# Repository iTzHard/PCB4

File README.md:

# PCB4

Minimalist 38 key keyboard designed for BVC2013, the layout is derived from The Card by Ben Vallack.

I don't plan to order this design, feel free to bug me on Discord or Twitter if you find any problems or need any help.

[Absolem Club](https://discord.gg/JM7XwHd746)

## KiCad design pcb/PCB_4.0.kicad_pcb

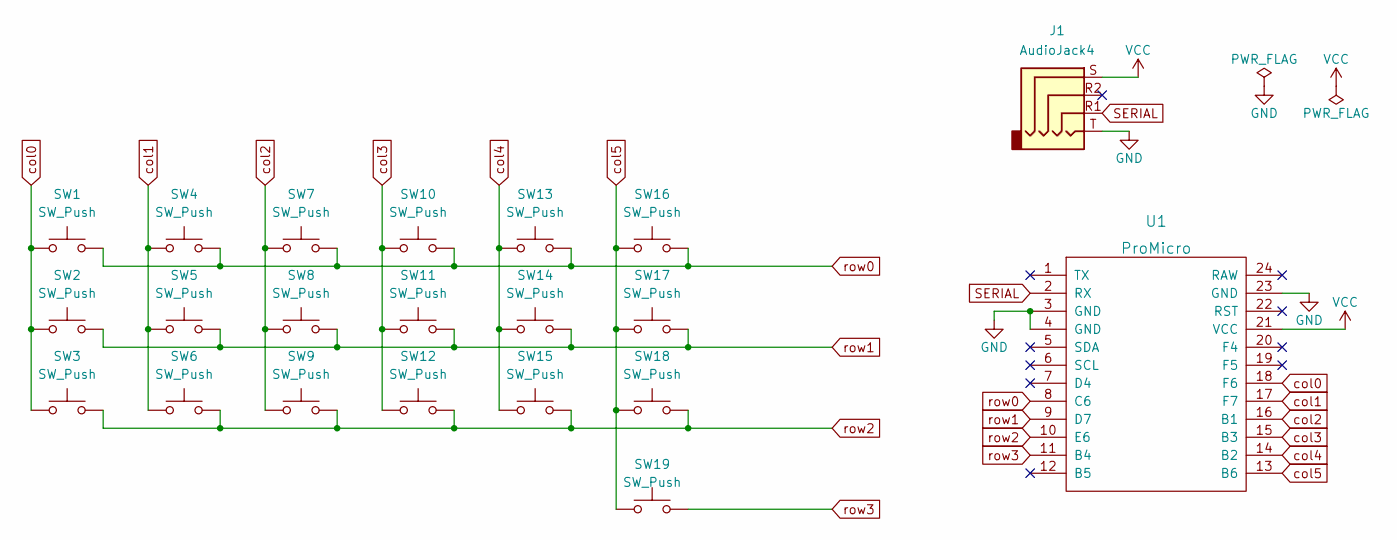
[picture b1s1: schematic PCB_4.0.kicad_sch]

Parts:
J1: AudioJack4; TRRS_crkbd
SW1, SW2, SW3, SW4, SW5, SW6, SW7, SW8, SW9, SW10, SW11, SW12, SW13, SW14, SW15, SW16, SW17, SW18, SW19: SW_Push; BVC2013_diode_courtyard
U1: ProMicro; OxyMoron

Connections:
GND: J1.T, U1.3 (GND), U1.4 (GND), U1.23 (GND)
SERIAL: J1.R1, U1.2 (RX)
VCC: J1.S, U1.21 (VCC)
col0: SW1.1, SW2.1, SW3.1, U1.18 (F6)
col1: SW4.1, SW5.1, SW6.1, U1.17 (F7)
col2: SW7.1, SW8.1, SW9.1, U1.16 (B1)
col3: SW10.1, SW11.1, SW12.1, U1.15 (B3)
col4: SW13.1, SW14.1, SW15.1, U1.14 (B2)
col5: SW16.1, SW17.1, SW18.1, SW19.1, U1.13 (B6)
row0: SW1.2, SW4.2, SW7.2, SW10.2, SW13.2, SW16.2, U1.8 (C6)
row1: SW2.2, SW5.2, SW8.2, SW11.2, SW14.2, SW17.2, U1.9 (D7)
row2: SW3.2, SW6.2, SW9.2, SW12.2, SW15.2, SW18.2, U1.10 (E6)
row3: SW19.2, U1.11 (B4)

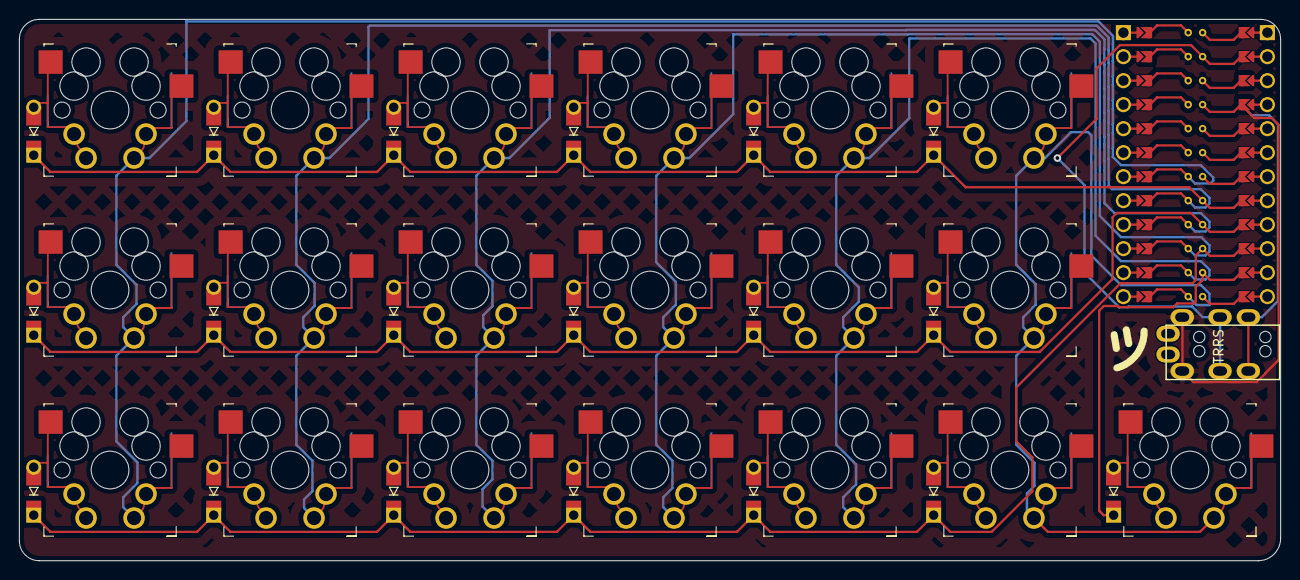
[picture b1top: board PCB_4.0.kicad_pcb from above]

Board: 2 copper layers, 133.5 x 57.3 mm, 21 parts (0 on the bottom side), 13 nets.

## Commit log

2022-02-16 Fix Discord link
